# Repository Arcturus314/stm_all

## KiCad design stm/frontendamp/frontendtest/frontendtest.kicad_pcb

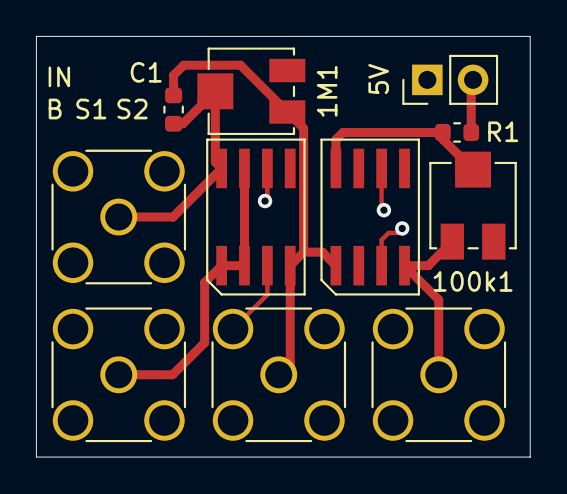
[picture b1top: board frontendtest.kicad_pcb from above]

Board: 4 copper layers, 27.4 x 23.4 mm, 11 parts (0 on the bottom side), 7 nets.

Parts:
1M1, 100k1: R_POT; Potentiometer_Bourns_3314J_Vertical
C1: 10pF; C_0603_1608Metric
J1, J3, J4, J5: Conn_Coaxial; SMA_Amphenol_132134_Vertical
J2: Conn_01x02_Male; PinHeader_1x02_P2.54mm_Vertical
R1: 1k; R_0603_1608Metric
U1, U2: lmp7721

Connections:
+10V: J2.1, U1.6, U2.6
GND: J1.2, J2.2, J3.2, J4.2, J5.2, R1.1, U1.3, U2.3
unnamed: 1M1.1, C1.2, J5.1, U1.4, U2.1
unnamed: 1M1.2, C1.1, J1.1, U1.8
unnamed: 100k1.1, J4.1, U2.4
unnamed: 100k1.2, R1.2, U2.8
unnamed: J3.1, U1.1, U1.2, U1.7

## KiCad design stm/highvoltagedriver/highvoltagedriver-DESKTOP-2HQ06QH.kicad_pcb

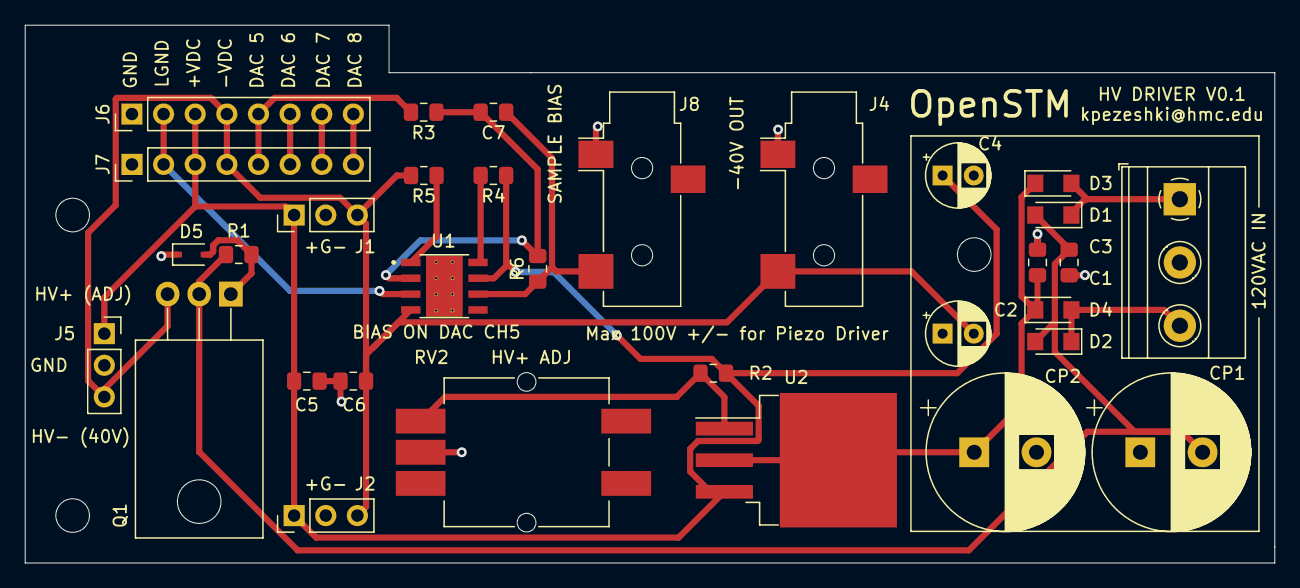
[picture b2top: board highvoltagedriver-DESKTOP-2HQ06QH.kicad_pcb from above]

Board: 2 copper layers, 100.3 x 43.2 mm, 32 parts (0 on the bottom side), 18 nets.

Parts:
C1, C3, C5, C6: 1uF; C_0805_2012Metric_Pad1.15x1.40mm_HandSolder
C2, C4: 10uF; CP_Radial_D5.0mm_P2.50mm
C7: 1nF; C_0805_2012Metric_Pad1.15x1.40mm_HandSolder
CP1, CP2: 200uF; CP_Radial_D12.5mm_P5.00mm
D1, D2, D3, D4: D; D_SMF
D5: D_Zener; D_SOD-323
J1, J2: Conn_01x03_Male; PinHeader_1x03_P2.54mm_Vertical
J3: Screw_Terminal_01x03; TerminalBlock_Phoenix_MKDS-1,5-3-5.08_1x03_P5.08mm_Horizont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
J4, J8: AudioJack2; Jack_3.5mm_CUI_SJ-3523-SMT_Horizontal
J5: Conn_01x03_Female; PinSocket_1x03_P2.54mm_Vertical
J6: Conn_01x08_Male; PinHeader_1x08_P2.54mm_Vertical
J7: Conn_01x08_Female; PinHeader_1x08_P2.54mm_Vertical
Q1: TIP127; TO-220-3_Horizontal_TabDown
R1: 10k; R_0805_2012Metric_Pad1.15x1.40mm_HandSolder
R2: 100; R_0805_2012Metric_Pad1.15x1.40mm_HandSolder
R3: 1k; R_0805_2012Metric_Pad1.15x1.40mm_HandSolder
R4, R5: 100K; R_0805_2012Metric_Pad1.15x1.40mm_HandSolder
R6: 50K; R_0805_2012Metric_Pad1.15x1.40mm_HandSolder
RV2: 10k; Potentiometer_Bourns_PRS11S_Vertical
U1: OPA454AIDDA; NOPB
U2: TL783; TO-263-3_TabPin2

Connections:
/DACBIAS: J6.5, J7.5, R3.2
/HVN: C2.2, C6.1, J1.3, J2.3, J4.T, J5.3, J6.4, J7.4, Q1.3, R5.2, U1.4
/HVP: C4.1, C5.1, J1.1, J2.1, J5.1, J6.3, J7.3, R2.2, R4.1, U1.7, U2.3
/biasamp/BIAS: J6.2, J7.2, U1.3
/biasamp/OUT: C7.1, J8.T, R6.1, U1.6
/hvpower/negreg/VNEG: C1.2, CP1.2, D1.2, D2.2, Q1.2, R1.2
GND: C1.1, C2.1, C3.2, C4.2, C5.2, C6.2, CP1.1, CP2.2, D5.1, J1.2, J2.2, J3.2, J4.S, J5.2, J6.1, J7.1, J8.S, RV2.2
unnamed: C3.1, CP2.1, D3.1, D4.1, U2.2
unnamed: C7.2, R3.1, R6.2, U1.2
unnamed: D1.1, D3.2, J3.1
unnamed: D2.1, D4.2, J3.3
unnamed: D5.2, Q1.1, R1.1
unnamed: J6.6, J7.6
unnamed: J6.7, J7.7
unnamed: J6.8, J7.8
unnamed: R2.1, RV2.1, U2.1
unnamed: R4.2, U1.8
unnamed: R5.1, U1.1

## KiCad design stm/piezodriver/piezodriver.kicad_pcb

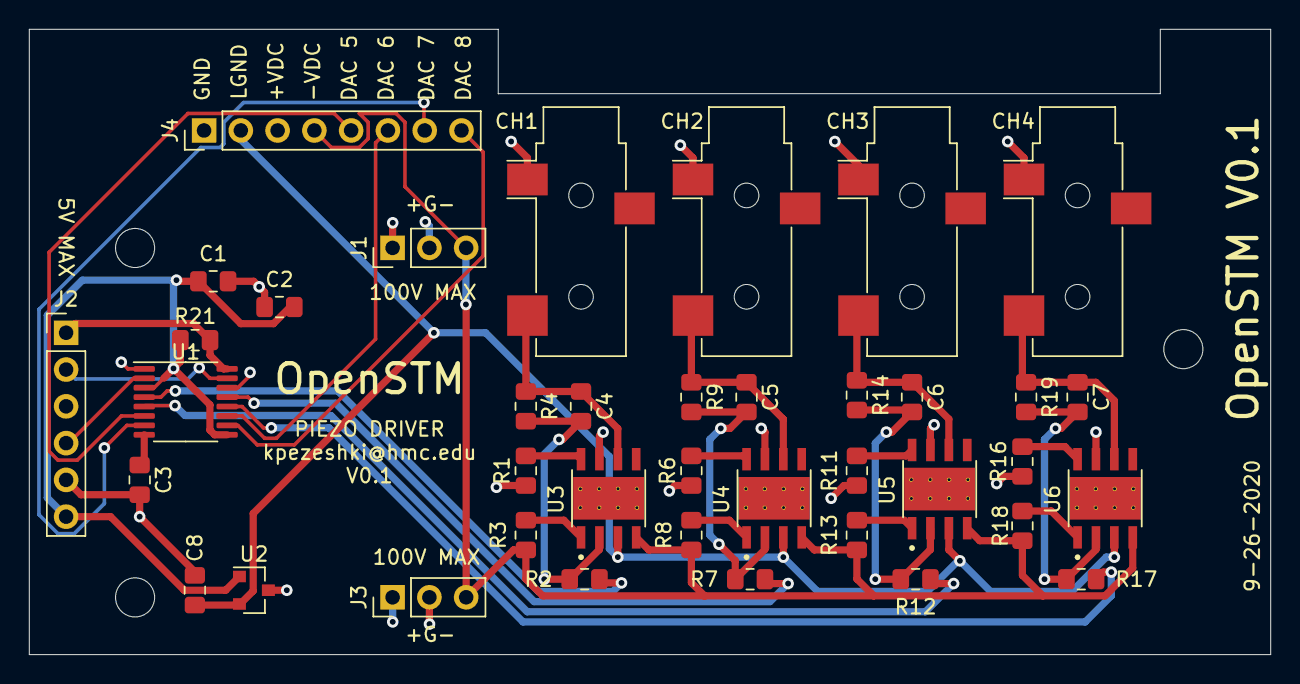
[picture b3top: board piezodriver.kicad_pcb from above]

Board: 4 copper layers, 85.7 x 43.2 mm, 39 parts (0 on the bottom side), 33 nets.

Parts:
C1: 10uF; C_0805_2012Metric_Pad1.15x1.40mm_HandSolder
C2, C3: 0.1uF; C_0805_2012Metric_Pad1.15x1.40mm_HandSolder
C4, C5, C6, C7: 1nF; C_0805_2012Metric_Pad1.15x1.40mm_HandSolder
C8: 1uF; C_0805_2012Metric_Pad1.15x1.40mm_HandSolder
J1, J3: Conn_01x03_Male; PinHeader_1x03_P2.54mm_Vertical
J2: Conn_01x06_Male; PinHeader_1x06_P2.54mm_Vertical
J4: Conn_01x08_Male; PinHeader_1x08_P2.54mm_Vertical
J5: CH2; Jack_3.5mm_CUI_SJ-3523-SMT_Horizontal
J6: CH3; Jack_3.5mm_CUI_SJ-3523-SMT_Horizontal
J7: CH4; Jack_3.5mm_CUI_SJ-3523-SMT_Horizontal
J8: CH1; Jack_3.5mm_CUI_SJ-3523-SMT_Horizontal
R1, R3, R6, R8, R11, R13, R16, R18: 100K; R_0805_2012Metric_Pad1.15x1.40mm_HandSolder
R2, R7, R12, R17: 1k; R_0805_2012Metric_Pad1.15x1.40mm_HandSolder
R4, R9, R14, R19: 50K; R_0805_2012Metric_Pad1.15x1.40mm_HandSolder
R21: 10k; R_0805_2012Metric_Pad1.15x1.40mm_HandSolder
U1: AD5628ARUZ-2; TSSOP-16_4.4x5mm_P0.65mm
U2: MAX6101; SOT-23
U3, U4, U5, U6: OPA454AIDDA; NOPB

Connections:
+VDC: J1.1, J3.1, J4.3, R1.1, R6.1, R11.1, R16.1, U3.7, U4.7, U5.7, U6.7
-VDC: J1.3, J3.3, J4.4, R3.2, R8.2, R13.2, R18.2, U3.4, U4.4, U5.4, U6.4
/CH5: J4.5, U1.6
/CH6: J4.6, U1.11
/CH7: J4.7, U1.7
/CH8: J4.8, U1.10
/opampdriver/BIAS: C8.1, J4.2, U2.2, U3.3, U4.3, U5.3, U6.3
/opampdriver/OUT: C4.1, J8.T, R4.1, U3.6
/opampdriver/SIG: R2.2, U1.4
/sheet5F77FFF0/OUT: C5.1, J5.T, R9.1, U4.6
/sheet5F77FFF0/SIG: R7.2, U1.13
/sheet5F780C4A/OUT: C7.1, J7.T, R19.1, U6.6
/sheet5F780C4A/SIG: R17.2, U1.12
/sheet5F78069E/OUT: C6.1, J6.T, R14.1, U5.6
/sheet5F78069E/SIG: R12.2, U1.5
GND: C1.2, C2.2, C3.2, C8.2, J1.2, J2.5, J3.2, J4.1, J5.S, J6.S, J7.S, J8.S, U1.1, U1.14, U2.3
unnamed: C3.1, U1.8
unnamed: C4.2, R2.1, R4.2, U3.2
unnamed: C5.2, R7.1, R9.2, U4.2
unnamed: C6.2, R12.1, R14.2, U5.2
unnamed: C7.2, R17.1, R19.2, U6.2
unnamed: J2.1, R21.2, U1.16
unnamed: J2.2, U1.15
unnamed: J2.4, U1.2
unnamed: R1.2, U3.8
unnamed: R3.1, U3.1
unnamed: R6.2, U4.8
unnamed: R8.1, U4.1
unnamed: R11.2, U5.8
unnamed: R13.1, U5.1
unnamed: R16.2, U6.8
unnamed: R18.1, U6.1
VCC: C1.1, C2.1, J2.6, R21.1, U1.3, U1.9, U2.1
